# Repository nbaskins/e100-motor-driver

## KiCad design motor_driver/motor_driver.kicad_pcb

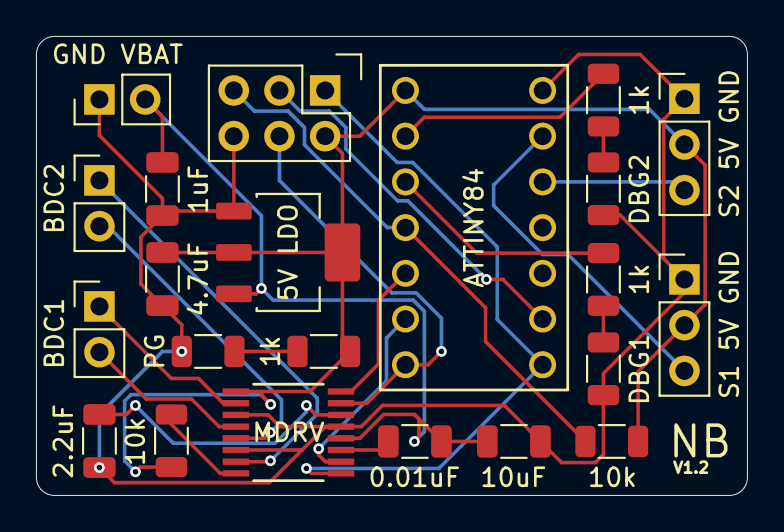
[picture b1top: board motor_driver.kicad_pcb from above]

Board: 2 copper layers, 39.5 x 25.5 mm, 22 parts (0 on the bottom side), 23 nets.

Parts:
0.01uF: 0.01uF; C_1206_3216Metric
1k, 1k#2, 1k#3: 1k; R_1206_3216Metric
1uF: 1uF; C_1206_3216Metric
2.2uF: 2.2uF; C_1206_3216Metric
4.7uF: 4.7uF; C_1206_3216Metric
5V LDO: LDL1117S50R_; SOT230P700X180-4N
10k, 10k#2: 10k; R_1206_3216Metric
10uF: 10uF; C_1206_3216Metric
ATTINY84: A14-LC-TT; A14-LC-TT_ASM
BDC1, BDC2: Conn_01x02_Pin; PinHeader_1x02_P2.54mm_Vertical
DBG1, DBG2: LED; R_1206_3216Metric
FLASH1: Conn_02x03_Odd_Even; PinHeader_2x03_P2.54mm_Vertical
GND VBAT: Conn_01x02_Pin; PinHeader_1x02_P2.54mm_Vertical
MDRV: DRV8833PWR
PG: LED; R_1206_3216Metric
S1 5V GND, S2 5V GND: Conn_01x03_Pin; PinHeader_1x03_P2.54mm_Vertical

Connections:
5V: 1k#2.1, 4.7uF.2, 5V LDO.2 (VOUT), 5V LDO.4 (VOUT__1), 10k.1, 10k#2.2, ATTINY84.1 (VCC), FLASH1.2, MDRV.1 (NSLEEP), S1 5V GND.2, S2 5V GND.2
GND: 1uF.1, 2.2uF.1, 4.7uF.1, 5V LDO.1 (GND), 10uF.1, ATTINY84.14 (GND), DBG1.1 (K), DBG2.1 (K), FLASH1.6, GND VBAT.1, MDRV.3 (AISEN), MDRV.6 (BISEN), MDRV.13 (GND), PG.1 (K), S1 5V GND.1, S2 5V GND.1
MISO: ATTINY84.8 (PA5), FLASH1.1, MDRV.9 (BIN1)
MOSI: ATTINY84.7 (PA6), FLASH1.4, MDRV.15 (AIN2)
unnamed: BDC1.1, MDRV.2 (AOUT1)
unnamed: BDC1.2, MDRV.4 (AOUT2)
unnamed: BDC2.1, MDRV.7 (BOUT1)
unnamed: BDC2.2, MDRV.5 (BOUT2)
unnamed: 1k.2, DBG1.2 (A)
unnamed: 1k#3.2, DBG2.2 (A)
unnamed: 1k#2.2, PG.2 (A)
unnamed: ATTINY84.13 (PA0), S1 5V GND.3
unnamed: ATTINY84.12 (PA1), S2 5V GND.3
unnamed: 1k#3.1, ATTINY84.2 (PB0)
unnamed: 1k.1, ATTINY84.3 (PB1)
unnamed: 10k#2.1, MDRV.8 (NFAULT)
unnamed: 0.01uF.2, MDRV.11 (VCP)
unnamed: 2.2uF.2, MDRV.14 (VINT)
PWMA0: ATTINY84.5 (PB2), MDRV.16 (AIN1)
PWMB0: ATTINY84.6 (PA7), MDRV.10 (BIN2)
RESET: 10k.2, ATTINY84.4 (RESET), FLASH1.5
SCK: ATTINY84.9 (PA4), FLASH1.3
VBAT: 0.01uF.1, 1uF.2, 5V LDO.3 (VIN), 10uF.2, GND VBAT.2, MDRV.12 (VM)

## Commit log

2026-04-16 added kicad files and firmware
2026-04-16 added watchdog to motordriver fw and renamed kicad project
2026-04-23 updated pcb schematic with changes from testing
2026-04-23 removed test code
